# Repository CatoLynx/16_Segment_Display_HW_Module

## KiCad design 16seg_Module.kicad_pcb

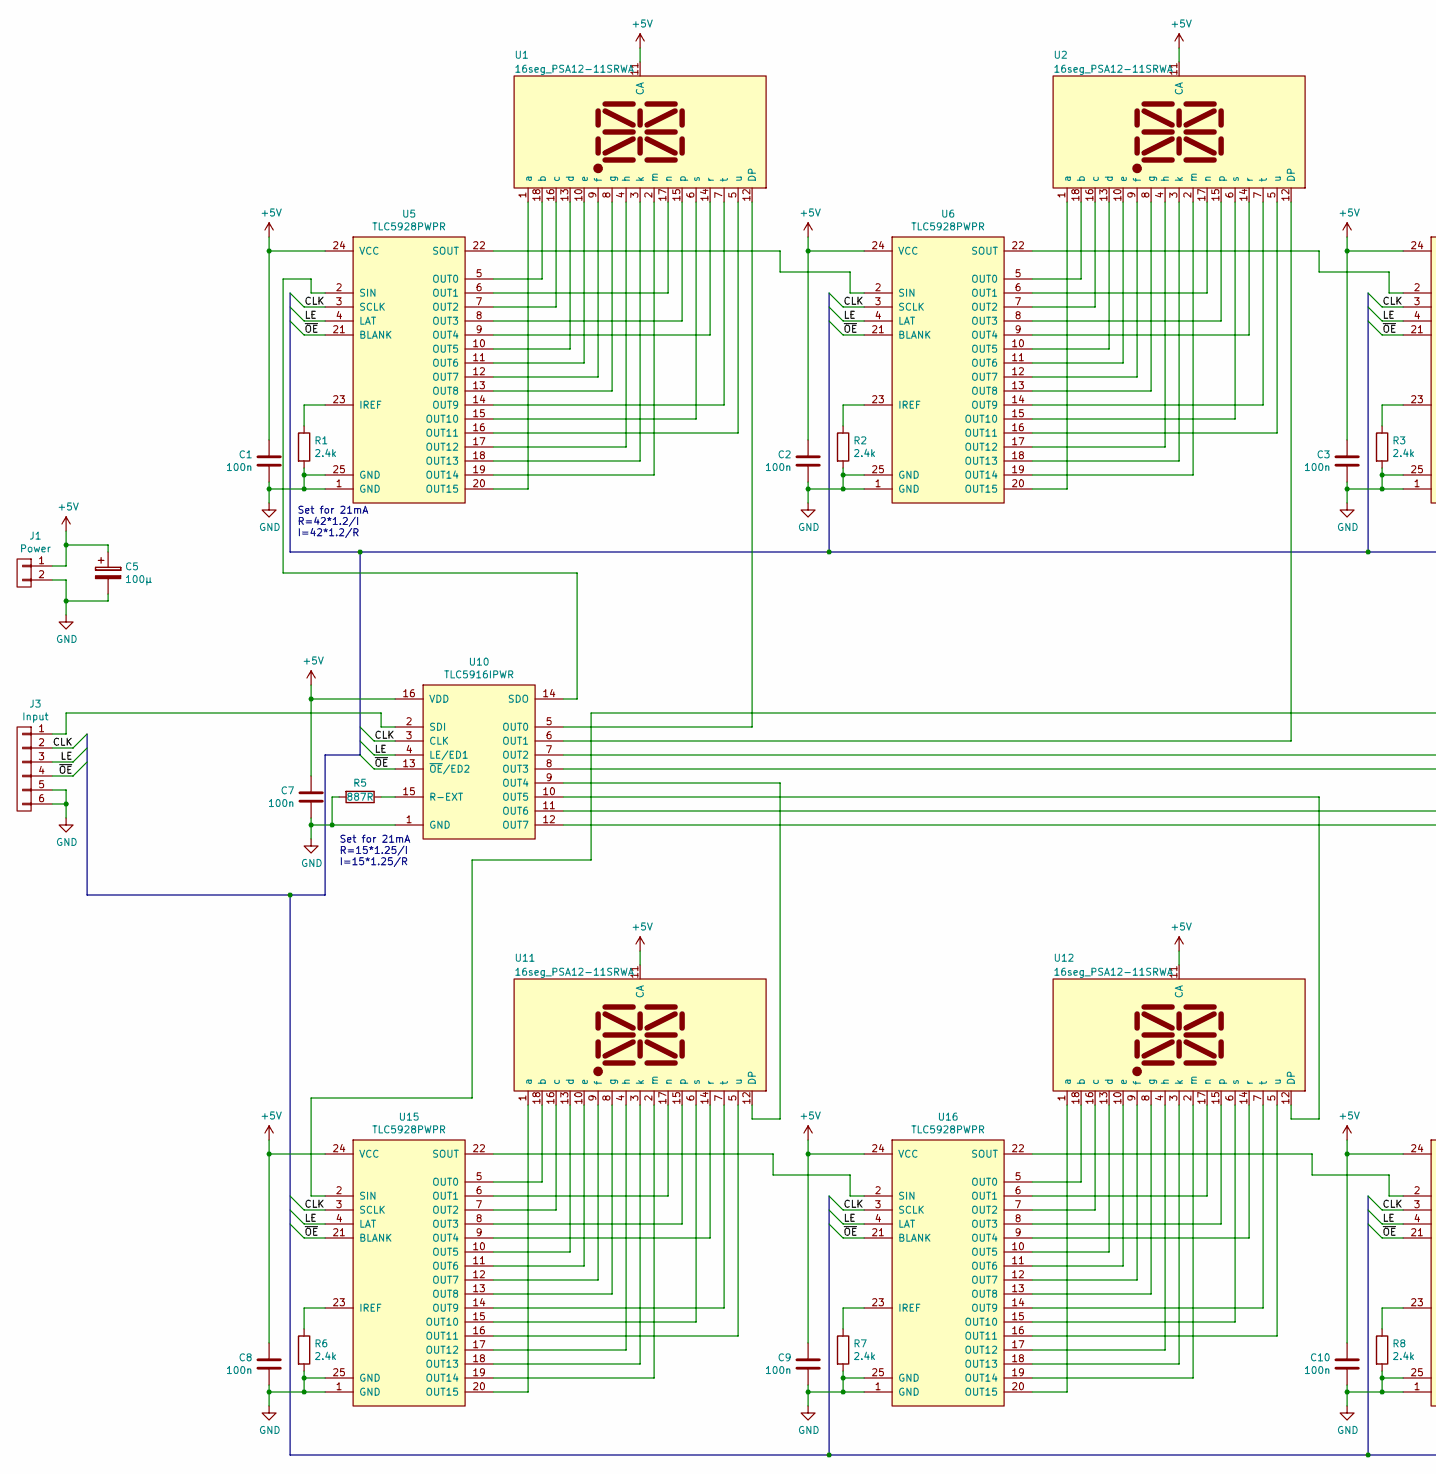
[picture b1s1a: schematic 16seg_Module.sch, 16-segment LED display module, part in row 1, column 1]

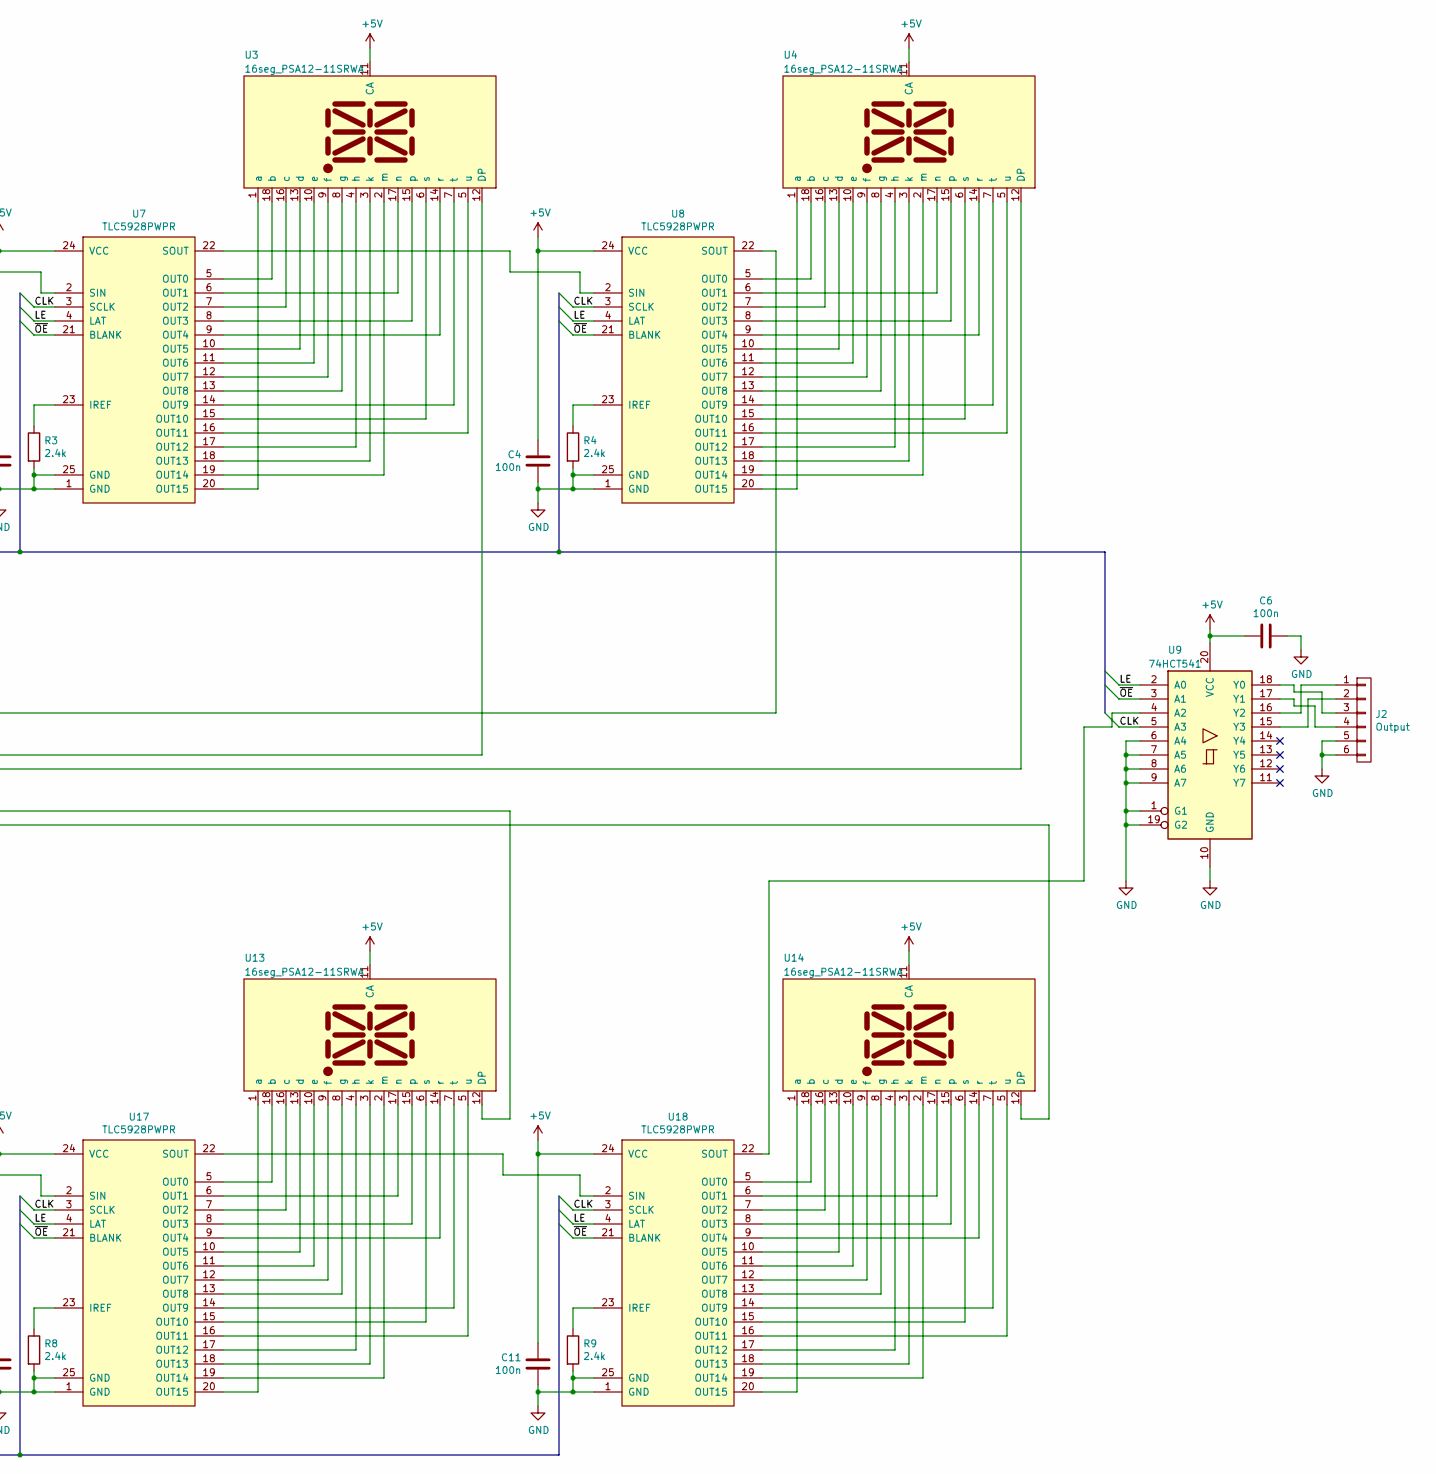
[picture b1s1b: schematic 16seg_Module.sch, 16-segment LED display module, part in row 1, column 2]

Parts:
C1, C2, C3, C4, C6, C7, C8, C9, C10, C11: 100n; C_0603
C5: 100µ; CP_Tantalum_Case-D_EIA-7343-31_Reflow
J1: Power; Conn_P3.96mm_1x02_vertical_THT
J2: Output; Conn_IDC_2x3_SMD
J3: Input; Conn_IDC_2x3_SMD
R1, R2, R3, R4, R6, R7, R8, R9: 2.4k; R_0603
R5: 887R; R_0603
U1, U2, U3, U4, U11, U12, U13, U14: 16seg_PSA12-11SRWA
U5, U6, U7, U8, U15, U16, U17, U18: TLC5928PWPR; TSSOP-24_EP_4.4x7.8mm_Pitch0.65mm
U9: 74HCT541; SOIC-20W_7.5x12.8mm_Pitch1.27mm
U10: TLC5916IPWR; TSSOP-16_4.4x5mm_Pitch0.65mm

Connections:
+5V: C1.2, C2.2, C3.2, C4.2, C5.1, C6.1, C7.2, C8.2, C9.2, C10.2, C11.2, J1.1, U1.11 (CA), U2.11 (CA), U3.11 (CA), U4.11 (CA), U5.24 (VCC), U6.24 (VCC), U7.24 (VCC), U8.24 (VCC), U9.20 (VCC), U10.16 (VDD), U11.11 (CA), U12.11 (CA), U13.11 (CA), U14.11 (CA), U15.24 (VCC), U16.24 (VCC), U17.24 (VCC), U18.24 (VCC)
/CLK: J3.2, U5.3 (SCLK), U6.3 (SCLK), U7.3 (SCLK), U8.3 (SCLK), U9.5 (A3), U10.3 (CLK), U15.3 (SCLK), U16.3 (SCLK), U17.3 (SCLK), U18.3 (SCLK)
/LE: J3.3, U5.4 (LAT), U6.4 (LAT), U7.4 (LAT), U8.4 (LAT), U9.2 (A0), U10.4 (LE/ED1), U15.4 (LAT), U16.4 (LAT), U17.4 (LAT), U18.4 (LAT)
/~OE: J3.4, U5.21 (BLANK), U6.21 (BLANK), U7.21 (BLANK), U8.21 (BLANK), U9.3 (A1), U10.13 (~OE~/ED2), U15.21 (BLANK), U16.21 (BLANK), U17.21 (BLANK), U18.21 (BLANK)
GND: C1.1, C2.1, C3.1, C4.1, C5.2, C6.2, C7.1, C8.1, C9.1, C10.1, C11.1, J1.2, J2.5, J2.6, J3.5, J3.6, R1.2, R2.2, R3.2, R4.2, R5.2, R6.2, R7.2, R8.2, R9.2, U5.1 (GND), U5.25 (GND), U6.1 (GND), U6.25 (GND), U7.1 (GND), U7.25 (GND), U8.1 (GND), U8.25 (GND), U9.1 (G1), U9.6 (A4), U9.7 (A5), U9.8 (A6), U9.9 (A7), U9.10 (GND), U9.19 (G2), U10.1 (GND), U15.1 (GND), U15.25 (GND), U16.1 (GND), U16.25 (GND), U17.1 (GND), U17.25 (GND), U18.1 (GND), U18.25 (GND)
unnamed: J2.1, U9.16 (Y2)
unnamed: J2.2, U9.15 (Y3)
unnamed: J2.3, U9.18 (Y0)
unnamed: J2.4, U9.17 (Y1)
unnamed: J3.1, U10.2 (SDI)
unnamed: R1.1, U5.23 (IREF)
unnamed: R2.1, U6.23 (IREF)
unnamed: R3.1, U7.23 (IREF)
unnamed: R4.1, U8.23 (IREF)
unnamed: R5.1, U10.15 (R-EXT)
unnamed: R6.1, U15.23 (IREF)
unnamed: R7.1, U16.23 (IREF)
unnamed: R8.1, U17.23 (IREF)
unnamed: R9.1, U18.23 (IREF)
unnamed: U1.1 (a), U5.20 (OUT15)
unnamed: U1.2 (m), U5.19 (OUT14)
unnamed: U1.3 (k), U5.18 (OUT13)
unnamed: U1.4 (h), U5.17 (OUT12)
unnamed: U1.5 (u), U5.16 (OUT11)
unnamed: U1.6 (s), U5.15 (OUT10)
unnamed: U1.7 (t), U5.14 (OUT9)
unnamed: U1.8 (g), U5.13 (OUT8)
unnamed: U1.9 (f), U5.12 (OUT7)
unnamed: U1.10 (e), U5.11 (OUT6)
unnamed: U1.12 (DP), U10.5 (OUT0)
unnamed: U1.13 (d), U5.10 (OUT5)
unnamed: U1.14 (r), U5.9 (OUT4)
unnamed: U1.15 (p), U5.8 (OUT3)
unnamed: U1.16 (c), U5.7 (OUT2)
unnamed: U1.17 (n), U5.6 (OUT1)
unnamed: U1.18 (b), U5.5 (OUT0)
unnamed: U2.1 (a), U6.20 (OUT15)
unnamed: U2.2 (m), U6.19 (OUT14)
unnamed: U2.3 (k), U6.18 (OUT13)
unnamed: U2.4 (h), U6.17 (OUT12)
unnamed: U2.5 (u), U6.16 (OUT11)
unnamed: U2.6 (s), U6.15 (OUT10)
unnamed: U2.7 (t), U6.14 (OUT9)
unnamed: U2.8 (g), U6.13 (OUT8)
unnamed: U2.9 (f), U6.12 (OUT7)
unnamed: U2.10 (e), U6.11 (OUT6)
unnamed: U2.13 (d), U6.10 (OUT5)
unnamed: U2.14 (r), U6.9 (OUT4)
unnamed: U2.15 (p), U6.8 (OUT3)
unnamed: U2.16 (c), U6.7 (OUT2)
unnamed: U2.17 (n), U6.6 (OUT1)
unnamed: U2.18 (b), U6.5 (OUT0)
unnamed: U3.1 (a), U7.20 (OUT15)
unnamed: U3.2 (m), U7.19 (OUT14)
unnamed: U3.3 (k), U7.18 (OUT13)
unnamed: U3.4 (h), U7.17 (OUT12)
unnamed: U3.5 (u), U7.16 (OUT11)
unnamed: U3.6 (s), U7.15 (OUT10)
unnamed: U3.7 (t), U7.14 (OUT9)
unnamed: U3.8 (g), U7.13 (OUT8)
unnamed: U3.9 (f), U7.12 (OUT7)
unnamed: U3.10 (e), U7.11 (OUT6)
unnamed: U3.13 (d), U7.10 (OUT5)
unnamed: U3.14 (r), U7.9 (OUT4)
unnamed: U3.15 (p), U7.8 (OUT3)
unnamed: U3.16 (c), U7.7 (OUT2)
unnamed: U3.17 (n), U7.6 (OUT1)
unnamed: U3.18 (b), U7.5 (OUT0)
unnamed: U4.1 (a), U8.20 (OUT15)
unnamed: U4.2 (m), U8.19 (OUT14)
unnamed: U4.3 (k), U8.18 (OUT13)
unnamed: U4.4 (h), U8.17 (OUT12)
unnamed: U4.5 (u), U8.16 (OUT11)
unnamed: U4.6 (s), U8.15 (OUT10)
unnamed: U4.7 (t), U8.14 (OUT9)
unnamed: U4.8 (g), U8.13 (OUT8)
unnamed: U4.9 (f), U8.12 (OUT7)
unnamed: U4.10 (e), U8.11 (OUT6)
unnamed: U4.13 (d), U8.10 (OUT5)
unnamed: U4.14 (r), U8.9 (OUT4)
unnamed: U4.15 (p), U8.8 (OUT3)
unnamed: U4.16 (c), U8.7 (OUT2)
unnamed: U4.17 (n), U8.6 (OUT1)
unnamed: U4.18 (b), U8.5 (OUT0)
unnamed: U5.22 (SOUT), U6.2 (SIN)
unnamed: U6.22 (SOUT), U7.2 (SIN)
unnamed: U7.22 (SOUT), U8.2 (SIN)
unnamed: U2.12 (DP), U10.6 (OUT1)
unnamed: U3.12 (DP), U10.7 (OUT2)
unnamed: U4.12 (DP), U10.8 (OUT3)
unnamed: U10.9 (OUT4), U11.12 (DP)
unnamed: U10.10 (OUT5), U12.12 (DP)
unnamed: U10.11 (OUT6), U13.12 (DP)
unnamed: U10.12 (OUT7), U14.12 (DP)
unnamed: U5.2 (SIN), U10.14 (SDO)
unnamed: U11.1 (a), U15.20 (OUT15)
unnamed: U11.2 (m), U15.19 (OUT14)
unnamed: U11.3 (k), U15.18 (OUT13)
unnamed: U11.4 (h), U15.17 (OUT12)
unnamed: U11.5 (u), U15.16 (OUT11)
unnamed: U11.6 (s), U15.15 (OUT10)
unnamed: U11.7 (t), U15.14 (OUT9)
unnamed: U11.8 (g), U15.13 (OUT8)
unnamed: U11.9 (f), U15.12 (OUT7)
unnamed: U11.10 (e), U15.11 (OUT6)
unnamed: U11.13 (d), U15.10 (OUT5)
unnamed: U11.14 (r), U15.9 (OUT4)
unnamed: U11.15 (p), U15.8 (OUT3)
unnamed: U11.16 (c), U15.7 (OUT2)
unnamed: U11.17 (n), U15.6 (OUT1)
unnamed: U11.18 (b), U15.5 (OUT0)
unnamed: U12.1 (a), U16.20 (OUT15)
unnamed: U12.2 (m), U16.19 (OUT14)
unnamed: U12.3 (k), U16.18 (OUT13)
unnamed: U12.4 (h), U16.17 (OUT12)
unnamed: U12.5 (u), U16.16 (OUT11)
unnamed: U12.6 (s), U16.15 (OUT10)
unnamed: U12.7 (t), U16.14 (OUT9)
unnamed: U12.8 (g), U16.13 (OUT8)
unnamed: U12.9 (f), U16.12 (OUT7)
unnamed: U12.10 (e), U16.11 (OUT6)
unnamed: U12.13 (d), U16.10 (OUT5)
unnamed: U12.14 (r), U16.9 (OUT4)
unnamed: U12.15 (p), U16.8 (OUT3)
unnamed: U12.16 (c), U16.7 (OUT2)
unnamed: U12.17 (n), U16.6 (OUT1)
unnamed: U12.18 (b), U16.5 (OUT0)
unnamed: U13.1 (a), U17.20 (OUT15)
unnamed: U13.2 (m), U17.19 (OUT14)
unnamed: U13.3 (k), U17.18 (OUT13)
unnamed: U13.4 (h), U17.17 (OUT12)
unnamed: U13.5 (u), U17.16 (OUT11)
unnamed: U13.6 (s), U17.15 (OUT10)
unnamed: U13.7 (t), U17.14 (OUT9)
unnamed: U13.8 (g), U17.13 (OUT8)
unnamed: U13.9 (f), U17.12 (OUT7)
unnamed: U13.10 (e), U17.11 (OUT6)
unnamed: U13.13 (d), U17.10 (OUT5)
unnamed: U13.14 (r), U17.9 (OUT4)
unnamed: U13.15 (p), U17.8 (OUT3)
unnamed: U13.16 (c), U17.7 (OUT2)
unnamed: U13.17 (n), U17.6 (OUT1)
unnamed: U13.18 (b), U17.5 (OUT0)
unnamed: U14.1 (a), U18.20 (OUT15)
unnamed: U14.2 (m), U18.19 (OUT14)
unnamed: U14.3 (k), U18.18 (OUT13)
unnamed: U14.4 (h), U18.17 (OUT12)
unnamed: U14.5 (u), U18.16 (OUT11)
unnamed: U14.6 (s), U18.15 (OUT10)
unnamed: U14.7 (t), U18.14 (OUT9)
unnamed: U14.8 (g), U18.13 (OUT8)
unnamed: U14.9 (f), U18.12 (OUT7)
unnamed: U14.10 (e), U18.11 (OUT6)
unnamed: U14.13 (d), U18.10 (OUT5)
unnamed: U14.14 (r), U18.9 (OUT4)
unnamed: U14.15 (p), U18.8 (OUT3)
unnamed: U14.16 (c), U18.7 (OUT2)
unnamed: U14.17 (n), U18.6 (OUT1)
unnamed: U14.18 (b), U18.5 (OUT0)
unnamed: U8.22 (SOUT), U15.2 (SIN)
unnamed: U15.22 (SOUT), U16.2 (SIN)
unnamed: U16.22 (SOUT), U17.2 (SIN)
unnamed: U17.22 (SOUT), U18.2 (SIN)
unnamed: U9.4 (A2), U18.22 (SOUT)

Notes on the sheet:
Set for 21mA R=42*1.2/I I=42*1.2/R
Set for 21mA R=15*1.25/I I=15*1.25/R

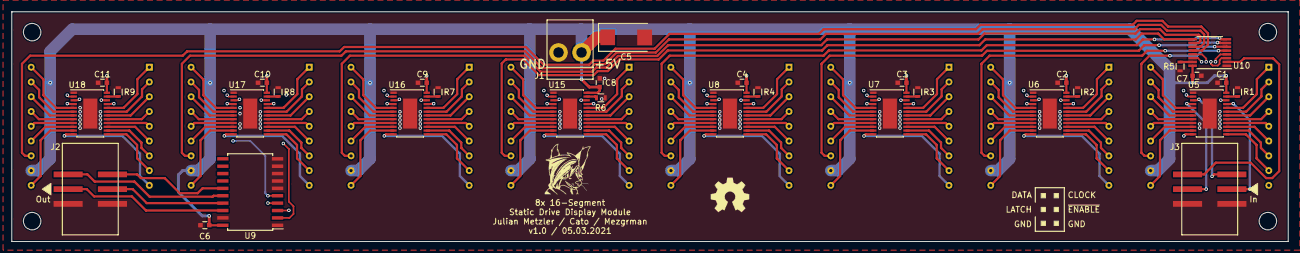
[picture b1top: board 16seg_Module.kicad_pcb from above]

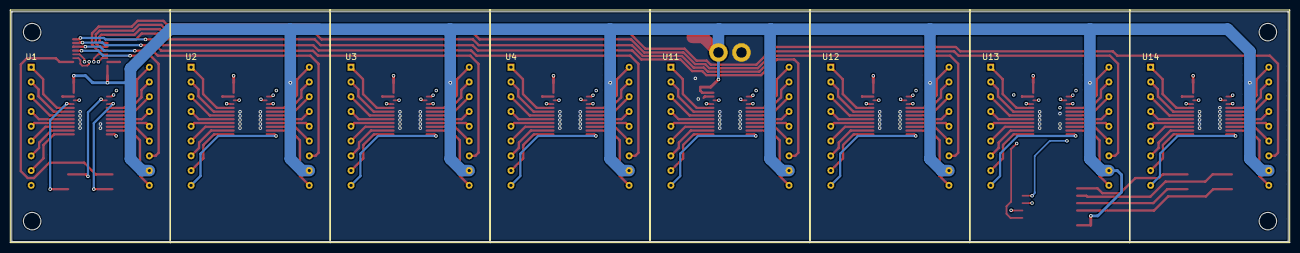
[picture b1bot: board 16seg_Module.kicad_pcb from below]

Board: 4 copper layers, 219.5 x 39.5 mm, 41 parts (8 on the bottom side), 164 nets.

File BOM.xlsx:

Item | Qty | Reference(s) | Value | LibPart | Footprint | Datasheet | Order No.
1 | 10 | C1,C2,C3,C4,C6,C7,C8,C9,C10,C11 | 100n | device:C | Capacitors_SMD:C_0603 | ~
2 | 1 | C5 | 100Âµ | device:CP | Capacitors_Tantalum_SMD:CP_Tantalum_Case-D_EIA-7343-31_Reflow | ~
3 | 1 | J1 | Power | conn:CONN_01X02 | custom:Conn_P3.96mm_1x02_vertical_THT
4 | 1 | J2 | Output | conn:CONN_01X06 | custom:Conn_IDC_2x3_SMD |  | T821M106A1S100CEUB
5 | 1 | J3 | Input | conn:CONN_01X06 | custom:Conn_IDC_2x3_SMD |  | T821M106A1S100CEUB
6 | 8 | R1,R2,R3,R4,R6,R7,R8,R9 | 2.4k | device:R | Resistors_SMD:R_0603 | ~
7 | 1 | R5 | 887R | device:R | Resistors_SMD:R_0603 | ~
8 | 8 | U1,U2,U3,U4,U11,U12,U13,U14 | 16seg_PSA12-11SRWA | custom:16seg_PSA12-11SRWA | custom:16seg_PSA12-11SRWA
9 | 8 | U5,U6,U7,U8,U15,U16,U17,U18 | TLC5928PWPR | custom:TLC5928_EP | custom:TSSOP-24_EP_4.4x7.8mm_Pitch0.65mm
10 | 1 | U9 | 74HCT541 | 74xx:74HCT541 | Housings_SOIC:SOIC-20W_7.5x12.8mm_Pitch1.27mm | http://www.ti.com/lit/gpn/sn74HCT541
11 | 1 | U10 | TLC5916IPWR | custom:TLC5916 | Housings_SSOP:TSSOP-16_4.4x5mm_Pitch0.65mm
